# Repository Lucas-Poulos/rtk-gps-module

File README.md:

# rtk-gps-module

A cheap, solder-down **RTK GNSS module** that gets you centimetre-level
position. Dual-band L1 + L5, castellated edges, and a USB-C port so it also
works on its own with nothing but a cable.

**Status: schematic complete and verified. PCB layout is the next phase.**

```
    ┌──── u.FL ────┐
    │ active       │   50 Ω CPWG, 0.38 mm
    │ dual-band    ├──► ESD ─► bias tee ─► DC block ─► π ─► SAW ─┐
    │ antenna      │    0.25pF   68 nH      100 pF    0R   L1+L5 │
    └──────────────┘        ▲                                    ▼
                            │                            ┌───────────────┐
                    ANT_ON ─┴─ PMOS switch               │   LC29H (DA)  │
                                                         │  dual-band    │
    USB-C ─► ESD ─► BAT54C OR ─► AP2112K 3V3 ────────────┤  RTK rover    │
      │                ▲                                 │               │
      │             5V_IN (carrier)                      │  UART1  1PPS  │
      └─► CH340N ──────────────────────────── UART ──────┤               │
                                        1k/10k divider   └───────┬───────┘
                                                                 │
                              24 castellated pads, 1.27 mm ──────┘
```

## What it does

Feed it **RTCM3 corrections** over the UART — from an NTRIP client on a
phone, a Raspberry Pi or a PC — and it resolves carrier phase to **1–2 cm
horizontal**, versus the 2–3 m you get from ordinary GPS.

Corrections come from the host, so there is **no radio on the board**:
nothing to license, nothing to certify, and one less thing to pay for.

| | |
|---|---|
| Receiver | Quectel LC29H (DA), dual-band RTK rover |
| Bands | L1 / E1 / B1 / G1 **and** L5 / E5a / B2a |
| Constellations | GPS, GLONASS, Galileo, BeiDou, QZSS, SBAS |
| RTK accuracy | ~1–2 cm CEP, open sky |
| **RTK fix rate** | **1 Hz** — the DA does not go faster, see below |
| Position rate, no RTK | up to 10 Hz |
| Corrections in | RTCM3 over UART1 — MSM4 or MSM7, plus 1005/1006 |
| Timing out | 1PPS, rising-edge synchronised |
| Supply | 5 V from USB-C **or** 5 V from the carrier board |
| Logic | 3.3 V (plus a 1.8 V debug domain, see below) |
| Interface | USB-C (CH340N) and 24 castellated pads on 1.27 mm |
| **Parts cost** | **$27.10** per board at qty 1 |

The receiver is **88 % of the bill**. Everything else together is $1.56.
Nothing but the receiver is worth cost-optimising.

### RTK fixes at 1 Hz, and only 1 Hz

Quectel's *LC29H (BA,CA,DA,EA) DR&RTK Application Note* is unambiguous:

> LC29H (DA) only supports RTK (update rate: 1 Hz).
> LC29H (EA) only supports RTK (update rate: 1–10 Hz, 10 Hz by default).

The 10 Hz figure quoted for these modules is the ordinary position rate.
With RTK engaged, the DA produces **one fix per second**. If you need
faster, the only variant that does it is the **EA**, which costs roughly
25 % more than the DA and is a different board cost, not a firmware
setting.

This also means the **AA variant gives up nothing on rate**. Its raw
observations are capped at 1 Hz, which is exactly what the DA fixes at —
so "the AA is slower" is not a real objection to moving the RTK engine
onto the host.

### Where the corrections come from

The board has no radio, so RTCM3 arrives over UART1 from whatever the host
can reach. In the United States most states run a free CORS network.

In Massachusetts that is **MaCORS**, MassDOT's 22-station SpiderNet
network covering all 14 counties, free after registration at
`macors.massdot.state.ma.us`. It serves RTCM 3.1 and RTCM 3.2 MSM4.

That is directly compatible — no translation layer. The DA accepts:

| Message | |
|---|---|
| 1005 / 1006 | Stationary RTK Reference Station ARP |
| 1074 / 1077 | GPS MSM4 / MSM7 |
| 1084 / 1087 | GLONASS MSM4 / MSM7 |
| 1094 / 1097 | Galileo MSM4 / MSM7 |
| 1114 / 1117 | QZSS MSM4 / MSM7 |
| 1124 / 1127 | BeiDou MSM4 / MSM7 |

If the network offers a VRS mount point it synthesises a virtual base at
your position, so the usual "stay within ~1 km of the base" rule stops
applying — the effective baseline is short wherever you are inside the
network. Outside network coverage that rule returns, and the answer is
your own base: **`LC29HBS` is the base-station variant and shares this
footprint**, so a second board off the same fab run becomes one.

### Multipath will dominate your results before the board does

RTK resolves carrier phase, and carrier phase is ruined by reflections.
A signal bounced off a glass facade arrives with corrupted phase, which
costs you the fix — or worse, buys a confident but wrong one.

Test open-sky first and separate the two questions: *does the board work*
and *does it work where I need it*. Debugging the former in an urban
canyon wastes days.

## Everything else is discrete

There is no way to make an RTK receiver from discrete components — carrier
phase needs a correlator ASIC. So the receiver and its SAW filter are ICs
and *everything around them* is built from single transistors and passives
rather than bought as a block:

- **Antenna bias tee** — a 68 nH choke, a 100 pF block, and a PMOS/NPN pair
  switched by `ANT_ON`, with a 10 Ω resistor limiting a shorted antenna to
  ~330 mA.
- **5 V ORing** — one BAT54C, anodes to USB and to the carrier's 5 V,
  cathode to the LDO. USB and carrier power can both be present and neither
  back-feeds the other.
- **Backup domain** — a second BAT54C ORs 3V3 with an optional external
  cell on `VBCKP_EXT`, so the ephemeris cache survives and the module
  hot-starts in ~1 s instead of cold-starting in ~30 s.
- **RX level shift** — a 1 k / 10 k divider, because `RXD1` is specified
  VIHmax **3.08 V** and a 3.3 V host would exceed it.
- **1PPS indicator** — one MMBT3904, because 1PPS is guaranteed only 2.1 V
  high and would drive an LED dimly while loading the edge.

## The impedance work

Fully derived rather than asserted — see **[docs/impedance.md](docs/impedance.md)**.
Short version:

- The antenna line is a **conductor-backed CPWG**, not microstrip. Solving
  the conformal-mapping model for JLCPCB's 4-layer JLC04161H-3313 stackup
  gives **0.38 mm at 0.2 mm gap → 50.19 Ω**. Treating it as microstrip
  would say 0.41 mm and land it near 47 Ω.
- The SAW's ports are **50 Ω ∥ 5.1 nH**, not 50 Ω, so `L302`/`L303` are
  part of the impedance, not optional.
- The ESD diode is **0.25 pF**. An ordinary ESD part at 10–50 pF would
  shunt the antenna signal away.
- The number lives in `tools/calc_impedance.py`, and `make check` fails
  if the project's RF netclass drifts away from it.

## Pinout

24 castellated pads on 1.27 mm — drops onto 0.1 in perfboard.

**Left edge (J501)**

| Pad | Name | Notes |
|---:|---|---|
| 1 | GND | |
| 2 | 5V_IN | ORed with USB VBUS |
| 3 | 3V3 | LDO output |
| 4 | VBCKP_EXT | optional backup cell / supercap |
| 5 | GND | |
| 6 | TXD1 | receiver → host, NMEA / PQTM |
| 7 | RXD1 | host → receiver, RTCM3 in |
| 8 | 1PPS | rising edge |
| 9 | RESET_N | active low, pulled up on-board |
| 10 | WAKEUP | needs ≥ 3.0 V to wake |
| 11 | VDD_EXT | 2.8 V out, **100 mA max** |
| 12 | GND | |

**Right edge (J502)**

| Pad | Name | Notes |
|---:|---|---|
| 1 | GND | |
| 2 | ANT_ON | antenna switch control |
| 3 | I2C_SDA | via DNP link |
| 4 | I2C_SCL | via DNP link |
| 5 | TXD2 | **1.8 V domain**, via DNP link |
| 6 | RXD2 | **1.8 V domain**, via DNP link |
| 7 | D_SEL1 | **1.8 V domain**, via DNP link |
| 8 | D_SEL2 | **1.8 V domain**, via DNP link |
| 9 | GND | |
| 10–11 | — | spare |
| 12 | GND | |

> **Pads 5–8 on the right edge are not 3.3 V tolerant.** VIHmax is 2.1 V.
> Each reaches the edge only through an unfitted link, so a default board
> cannot present them to a 3.3 V host by accident.

`D_SEL1 = D_SEL2 = 0` selects UART1 and is the on-chip default via 75 kΩ
pulldowns, so the fitted board needs no strapping parts at all.

## Repository layout

```
design/        THE PROJECT. Open it in KiCad, edit it, save it.
  lib/         the two symbols and three footprints stock KiCad lacks
tools/         helpers that READ design/ -- none of them write to it
  check.py             ERC + netlist + sourcing + impedance
  gen_bom.py           BOM, read from the schematic
  calc_impedance.py    the 50 Ω derivation
  fetch_datasheets.py  pulls the vendor PDFs (not committed)
  bootstrap/           the generators that built v1 -- NOT authoritative
Makefile       run `make` to list every target
.githooks/     optional pre-commit hook, ERC errors only
manufacturing/ BOM.md, BOM-dnp.md, bom_jlcpcb.csv
docs/          editing.md, impedance.md, schematic.pdf
datasheets/    README + fetch script; the PDFs are not ours to redistribute
analysis/      ERC report and netlist (gitignored, regenerated on demand)
```

**`design/` is a normal KiCad project.** Edit it directly. Nothing
regenerates it, and nothing in `tools/` writes to it.

## Working on it

```bash
make open       # open in KiCad -- edit and save freely
make check      # ERC + netlist + sourcing + impedance, all read-only
make bom        # rebuild manufacturing/ after a parts change
make            # list every target
```

Read **[docs/editing.md](docs/editing.md)** before changing the RF path
or anything on the LC29H — there are four traps on this board that KiCad
will not warn you about (a 3.08 V limit on `RXD1`, a 1.8 V pin domain,
two supply pins that are outputs, and three pins that must float).

`make check` reads `design/` and never writes to it. It exports a fresh
netlist and a fresh ERC report and asserts against those:

- **ERC** — must be clean *and* the report must be newly written. A stale
  report from an earlier run reads exactly like a pass, and `kicad-cli`
  writes no report at all when the schematic fails to parse. Verified by
  injecting a deliberate fault and confirming ERC caught it on the right
  sub-sheet.
- **Netclass** — the exported per-net class is read back, because KiCad
  accepts a netclass pattern that matches nothing without complaining and
  a 50 Ω line silently falls back to the default track width. *(This
  caught a real bug: `/regex/` patterns are accepted by the file format
  and match nothing — KiCad uses wildcards, and local nets carry their
  sheet path.)*
- **Critical nets** — the RF chain, the bias tee and the RXD1 divider are
  asserted pin by pin, so none of them gets rerouted by accident. Rewire
  one on purpose and it tells you exactly what changed.
- **LC29H pin rules** — grounds grounded, the three RESERVED pins still
  floating, `VDD_EXT` never tied to 3V3.
- **Sourcing** — every fitted part must carry a resolved `Cxxxxx`.
- **Impedance** — the RF netclass width must still match what
  `tools/calc_impedance.py` derives, and still land within 5 % of 50 Ω.

## Building one

The BOM is in [manufacturing/BOM.md](manufacturing/BOM.md), with
`bom_jlcpcb.csv` ready for JLCPCB assembly and
[BOM-dnp.md](manufacturing/BOM-dnp.md) listing the unfitted options.

Prices and stock were read from LCSC on 2026-09-28 and frozen for
traceability — **re-check before ordering.** LC29H stock in particular was
thin (22 pcs). `LC29HBS` (`C21385845`) is the RTK *base station* variant and
`LC29HAA` (`C22403415`) has no RTK engine; both share the footprint, so
check you are buying the one you mean.

You also need an **active dual-band L1+L5 antenna** with NF < 1.5 dB, gain
< 17 dB, and its SAW ahead of its LNA.

## Caveats

- **Not built yet.** The schematic is verified; no board has been
  fabricated, so nothing here is confirmed against hardware.
- **The LC29H (DA) pinout is contested by its own datasheet.** Figure 4
  and Table 6 disagree about pins 15–19. The V1.3 revision history settles
  it in Table 6's favour (the changes applied only to the EA variant), and
  the design follows Table 6 — but those four pins reach the edge only
  through unfitted links, so the board is correct either way.
- Prices are a snapshot, not a quote.

## Licence

Hardware under [CERN-OHL-P v2](LICENSE); the scripts under the same terms.
Permissive — do what you like, no reciprocity required.

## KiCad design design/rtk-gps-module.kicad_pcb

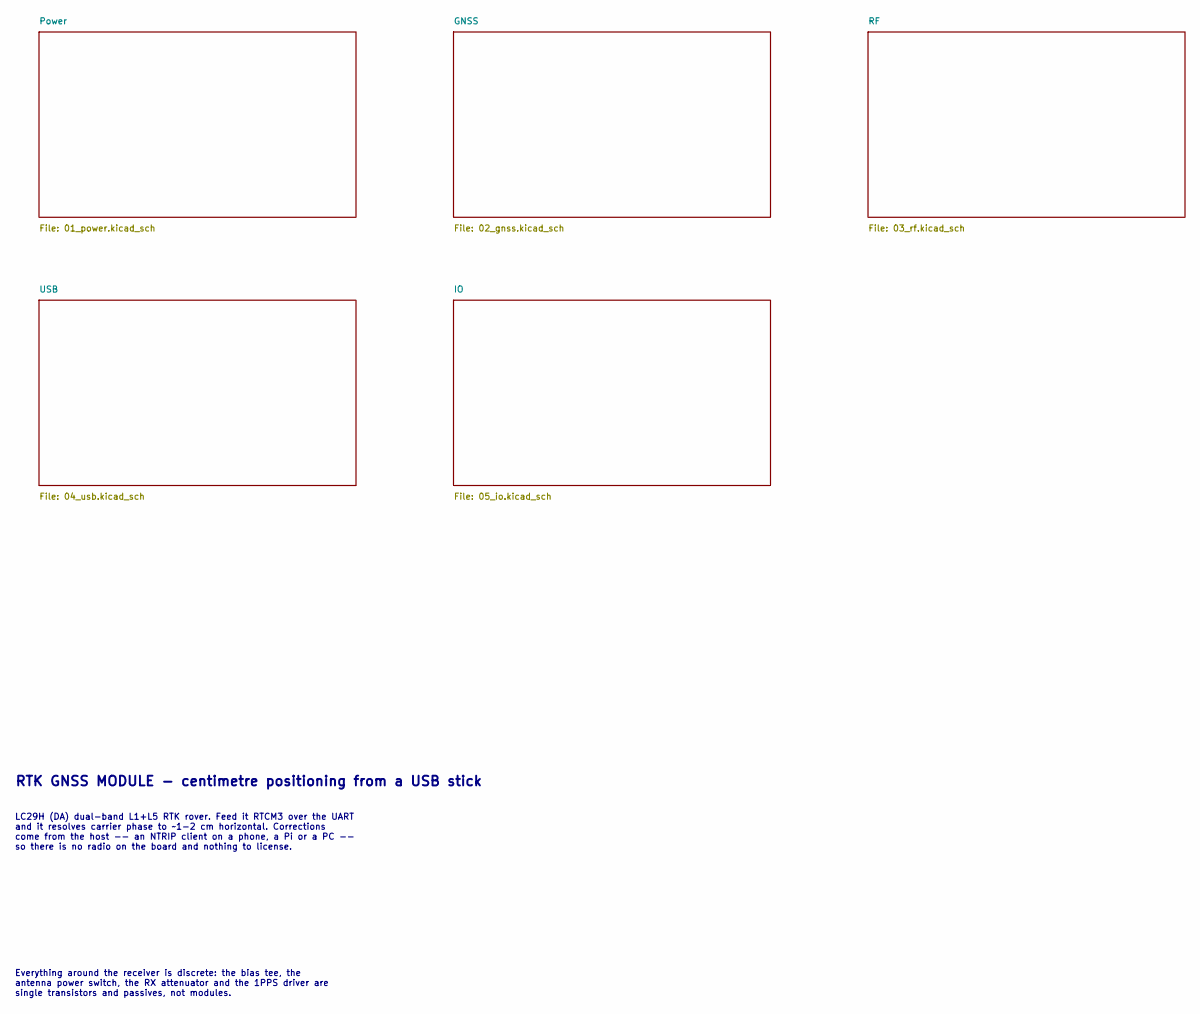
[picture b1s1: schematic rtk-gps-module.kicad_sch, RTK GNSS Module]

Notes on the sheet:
RTK GNSS MODULE - centimetre positioning from a USB stick
Everything around the receiver is discrete: the bias tee, the antenna power switch, the RX attenuator and the 1PPS driver are single transistors and passives, not modules.
LC29H (DA) dual-band L1+L5 RTK rover. Feed it RTCM3 over the UART and it resolves carrier phase to ~1-2 cm horizontal. Corrections come from the host -- an NTRIP client on a phone, a Pi or a PC -- so there is no radio on the board and nothing to license.

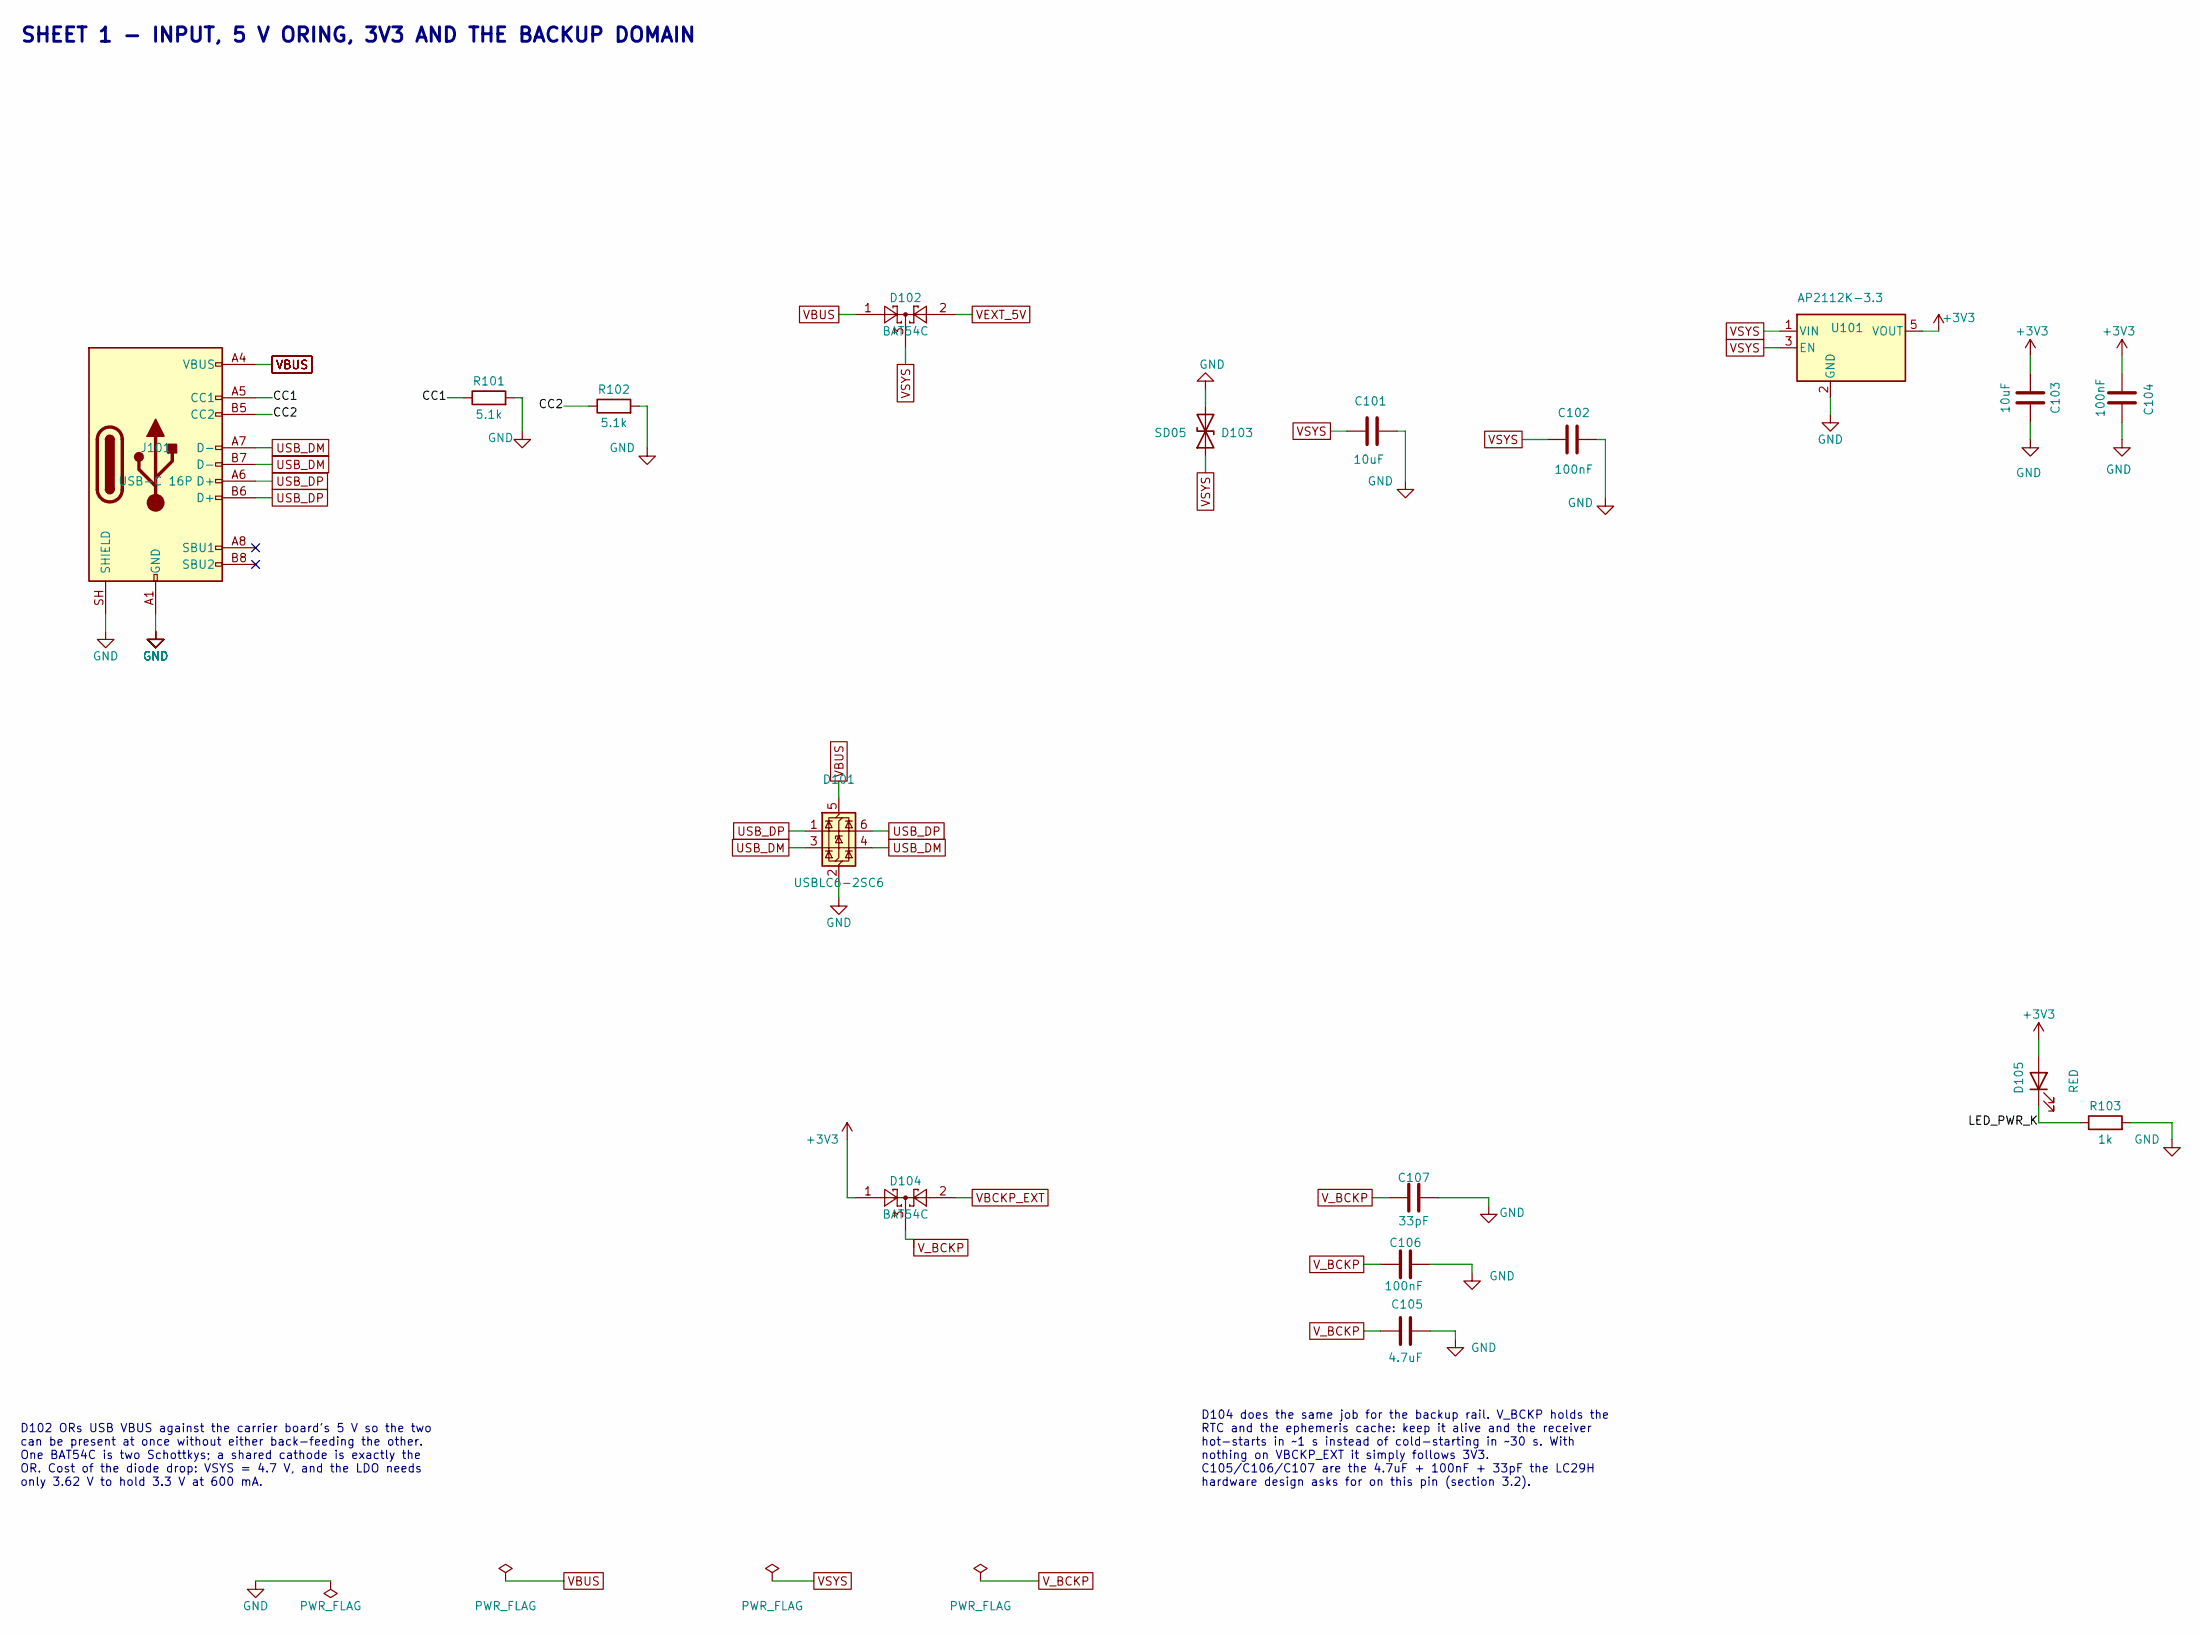
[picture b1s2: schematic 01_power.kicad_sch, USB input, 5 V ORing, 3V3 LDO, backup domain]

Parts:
C101, C103: 10uF; C_0805_2012Metric; MPN CL21A106KAYNNNE; LCSC C15850
C102, C104, C106: 100nF; C_0402_1005Metric; MPN CL05B104KO5NNNC; LCSC C1525
C105: 4.7uF; C_0603_1608Metric; MPN CL10A475KO8NNNC; LCSC C19666
C107: 33pF; C_0402_1005Metric; MPN 0402CG330J500NT; LCSC C1562
D101: USBLC6-2SC6; SOT-23-6; MPN USBLC6-2SC6; LCSC C2827654
D102, D104: BAT54C; SOT-23; MPN BAT54C; LCSC C916424
D103: SD05; D_SOD-323; MPN SD05; LCSC C502527
D105: RED; LED_0603_1608Metric; MPN KT-0603R; LCSC C2286
J101: USB-C 16P; USB_C_Receptacle_HRO_TYPE-C-31-M-12; MPN TYPE-C 16PIN 2MD(073); LCSC C2765186
R101, R102: 5.1k; R_0402_1005Metric; Tolerance 1%; MPN 0402WGF5101TCE; LCSC C25905
R103: 1k; R_0402_1005Metric; Tolerance 1%; MPN 0402WGF1001TCE; LCSC C11702
U101: AP2112K-3.3; SOT-23-5; MPN AP2112K-3.3TRG1; LCSC C23380830

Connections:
+3V3: C103.1, C104.1, D104.1, D105.2 (A), U101.5 (VOUT); also elsewhere on the board
/Power/CC1: J101.A5 (CC1), R101.1
/Power/CC2: J101.B5 (CC2), R102.1
/Power/LED_PWR_K: D105.1 (K), R103.1
GND: C101.2, C102.2, C103.2, C104.2, C105.2, C106.2, C107.2, D101.2 (GND), D103.2 (A2), J101.A1 (GND), J101.A12 (GND), J101.B1 (GND), J101.B12 (GND), J101.SH (SHIELD), R101.2, R102.2, R103.2, U101.2 (GND); also elsewhere on the board
USB_DM: D101.3 (I/O2), D101.4 (I/O2), J101.A7 (D-), J101.B7 (D-); also elsewhere on the board
USB_DP: D101.1 (I/O1), D101.6 (I/O1), J101.A6 (D+), J101.B6 (D+); also elsewhere on the board
VBCKP_EXT: D104.2; also elsewhere on the board
VBUS: D101.5 (VBUS), D102.1, J101.A4 (VBUS), J101.A9 (VBUS), J101.B4 (VBUS), J101.B9 (VBUS)
VEXT_5V: D102.2; also elsewhere on the board
VSYS: C101.1, C102.1, D102.3, D103.1 (A1), U101.1 (VIN), U101.3 (EN)
V_BCKP: C105.1, C106.1, C107.1, D104.3; also elsewhere on the board

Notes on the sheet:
D102 ORs USB VBUS against the carrier board's 5 V so the two can be present at once without either back-feeding the other. One BAT54C is two Schottkys; a shared cathode is exactly the OR. Cost of the diode drop: VSYS = 4.7 V, and the LDO needs only 3.62 V to hold 3.3 V at 600 mA.
SHEET 1 - INPUT, 5 V ORING, 3V3 AND THE BACKUP DOMAIN
D104 does the same job for the backup rail. V_BCKP holds the RTC and the ephemeris cache: keep it alive and the receiver hot-starts in ~1 s instead of cold-starting in ~30 s. With nothing on VBCKP_EXT it simply follows 3V3. C105/C106/C107 are the 4.7uF + 100nF + 33pF the LC29H hardware design asks 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

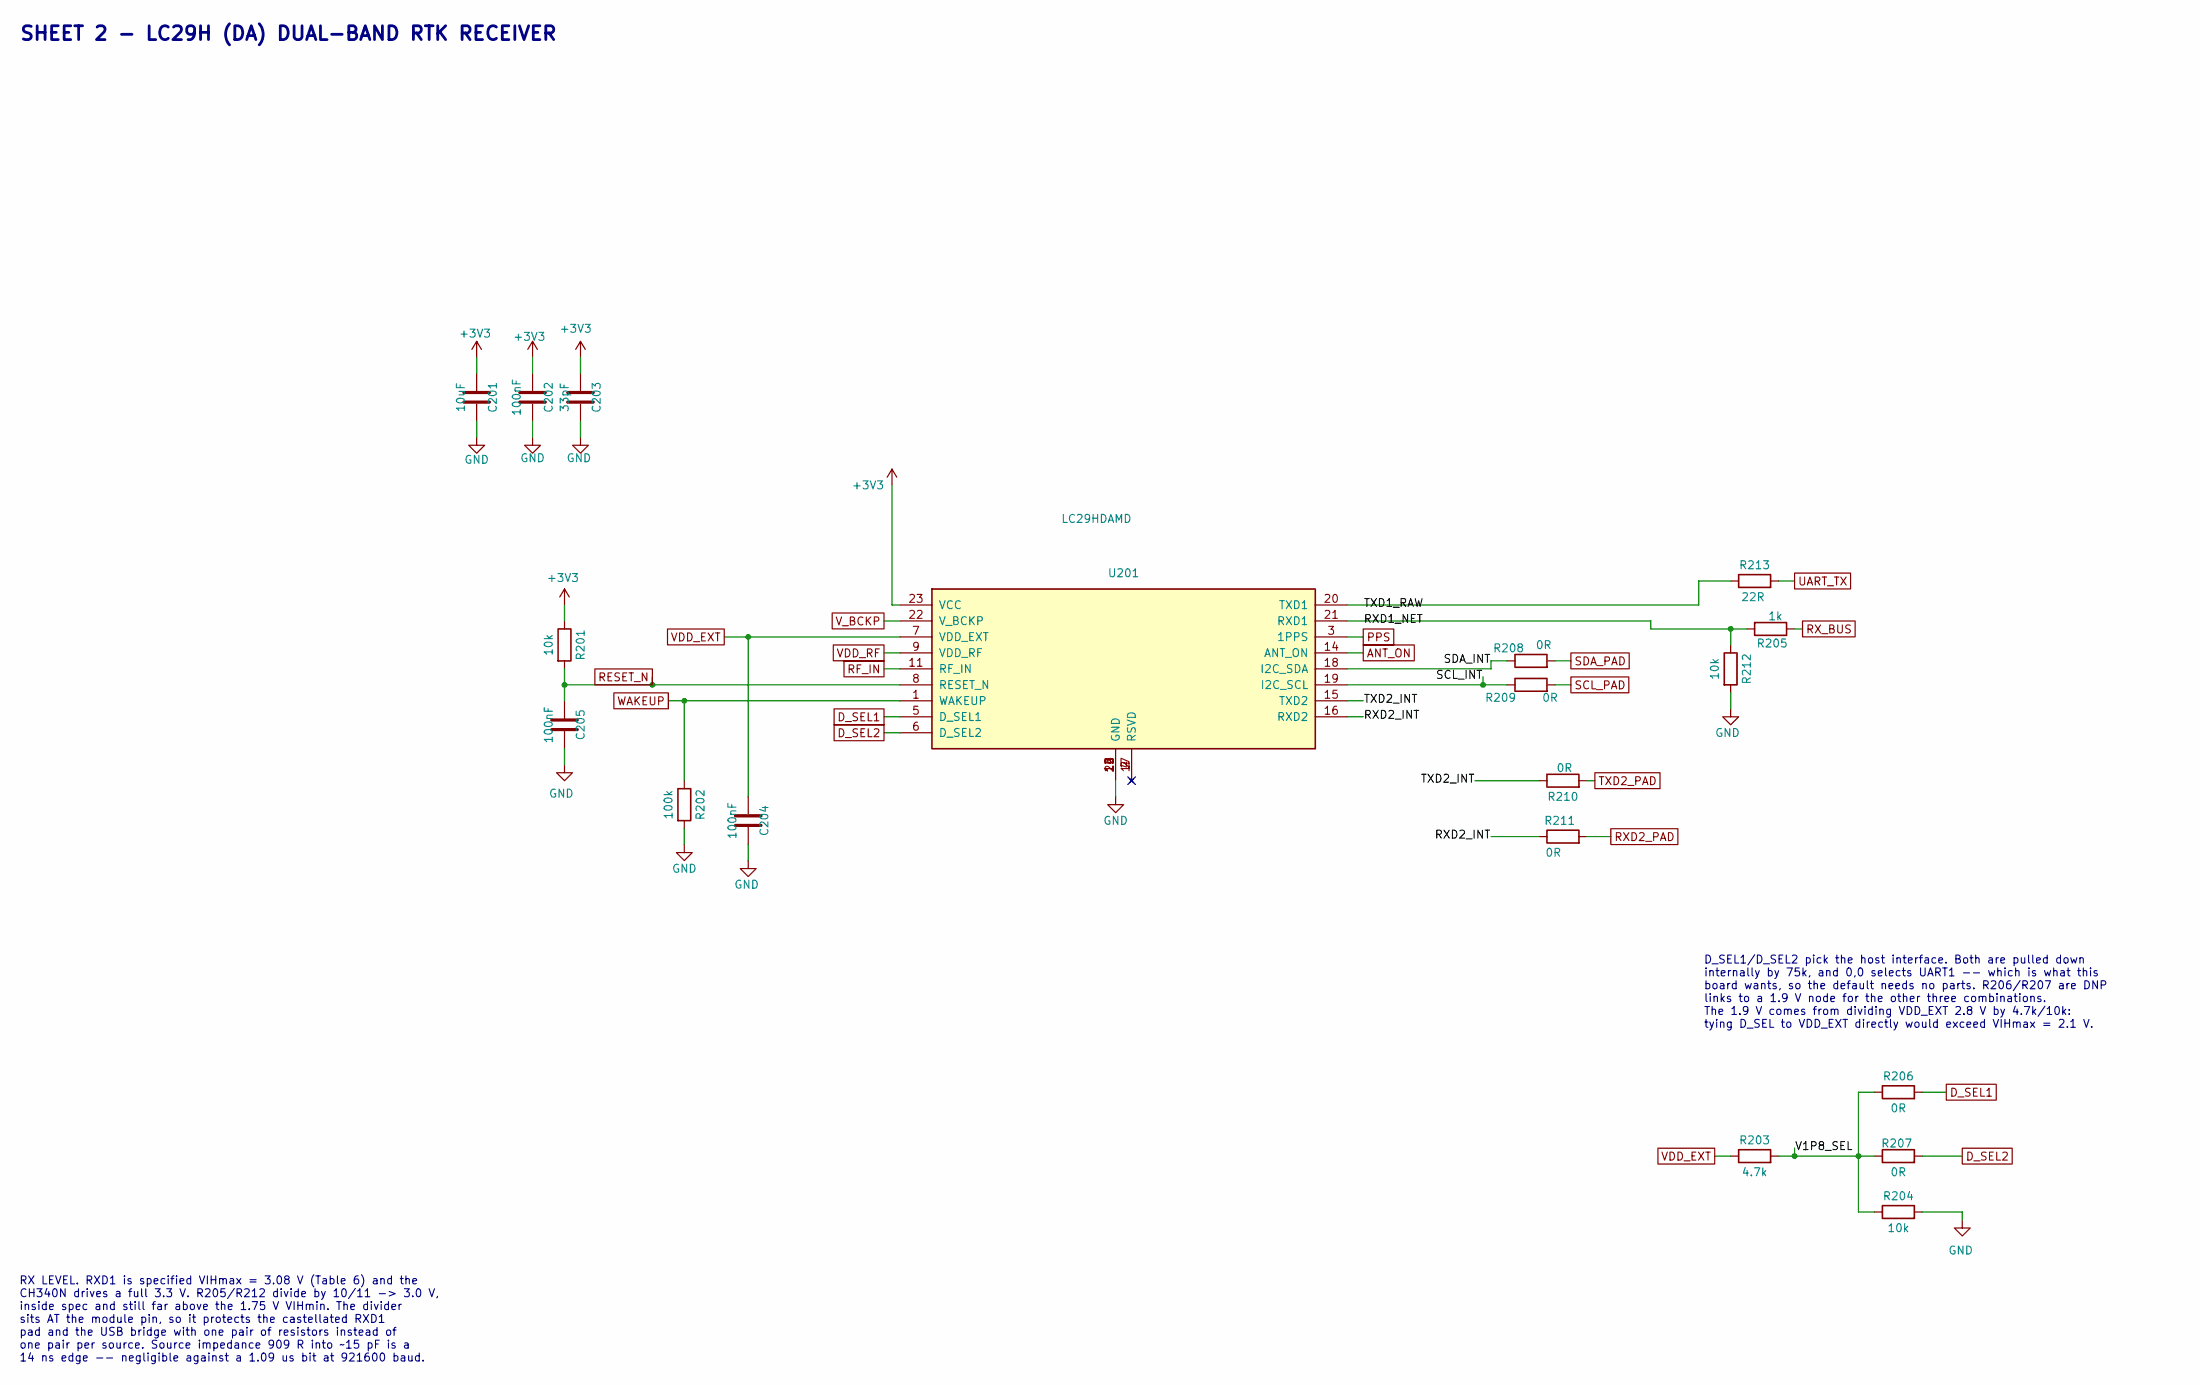
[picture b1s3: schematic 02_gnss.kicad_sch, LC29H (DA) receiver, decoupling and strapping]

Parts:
C201: 10uF; C_0805_2012Metric; MPN CL21A106KAYNNNE; LCSC C15850
C202, C204, C205: 100nF; C_0402_1005Metric; MPN CL05B104KO5NNNC; LCSC C1525
C203: 33pF; C_0402_1005Metric; MPN 0402CG330J500NT; LCSC C1562
R201, R204, R212: 10k; R_0402_1005Metric; Tolerance 1%; MPN 0402WGF1002TCE; LCSC C25744
R202: 100k; R_0402_1005Metric; Tolerance 1%; MPN 0402WGF1003TCE; LCSC C25741
R203: 4.7k; R_0402_1005Metric; Tolerance 1%; MPN 0402WGF4701TCE; LCSC C25900
R205: 1k; R_0402_1005Metric; Tolerance 1%; MPN 0402WGF1001TCE; LCSC C11702
R206, R207, R208, R209, R210, R211: 0R; R_0402_1005Metric; Tolerance 1%; MPN 0402WGF0000TCE; LCSC C17168
R213: 22R; R_0402_1005Metric; Tolerance 1%; MPN 0402WGF220JTCE; LCSC C25092
U201: LC29HDAMD; Quectel_LC29H_LCC-24_12.2x16.0mm; MPN LC29HDAMD; LCSC C20748061

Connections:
+3V3: C201.1, C202.1, C203.1, R201.1, U201.23 (VCC); also elsewhere on the board
/GNSS/RXD1_NET: R205.2, R212.1, U201.21 (RXD1)
/GNSS/RXD2_INT: R211.1, U201.16 (RXD2)
/GNSS/SCL_INT: R209.1, U201.19 (I2C_SCL)
/GNSS/SDA_INT: R208.1, U201.18 (I2C_SDA)
/GNSS/TXD1_RAW: R213.1, U201.20 (TXD1)
/GNSS/TXD2_INT: R210.1, U201.15 (TXD2)
/GNSS/V1P8_SEL: R203.2, R204.1, R206.1, R207.1
ANT_ON: U201.14 (ANT_ON); also elsewhere on the board
D_SEL1: R206.2, U201.5 (D_SEL1); also elsewhere on the board
D_SEL2: R207.2, U201.6 (D_SEL2); also elsewhere on the board
GND: C201.2, C202.2, C203.2, C204.2, C205.2, R202.2, R204.2, R212.2, U201.10 (GND), U201.12 (GND), U201.13 (GND), U201.24 (GND); also elsewhere on the board
PPS: U201.3 (1PPS); also elsewhere on the board
RESET_N: C205.1, R201.2, U201.8 (RESET_N); also elsewhere on the board
RF_IN: U201.11 (RF_IN); also elsewhere on the board
RXD2_PAD: R211.2; also elsewhere on the board
RX_BUS: R205.1; also elsewhere on the board
SCL_PAD: R209.2; also elsewhere on the board
SDA_PAD: R208.2; also elsewhere on the board
TXD2_PAD: R210.2; also elsewhere on the board
UART_TX: R213.2; also elsewhere on the board
VDD_EXT: C204.1, R203.1, U201.7 (VDD_EXT); also elsewhere on the board
VDD_RF: U201.9 (VDD_RF); also elsewhere on the board
V_BCKP: U201.22 (V_BCKP); also elsewhere on the board
WAKEUP: R202.1, U201.1 (WAKEUP); also elsewhere on the board

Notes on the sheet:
D_SEL1/D_SEL2 pick the host interface. Both are pulled down internally by 75k, and 0,0 selects UART1 -- which is what this board wants, so the default needs no parts. R206/R207 are DNP links to a 1.9 V node for the other three combinations. The 1.9 V comes from dividing VDD_EXT 2.8 V by 4.7k/10k: t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
RX LEVEL. RXD1 is specified VIHmax = 3.08 V (Table 6) and the CH340N drives a full 3.3 V. R205/R212 divide by 10/11 -> 3.0 V, inside spec and still far above the 1.75 V VIHmin. The divider sits AT the module pin, so it protects the castellated RXD1 pad and the USB bridge with one pair of resistors 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
SHEET 2 - LC29H (DA) DUAL-BAND RTK RECEIVER

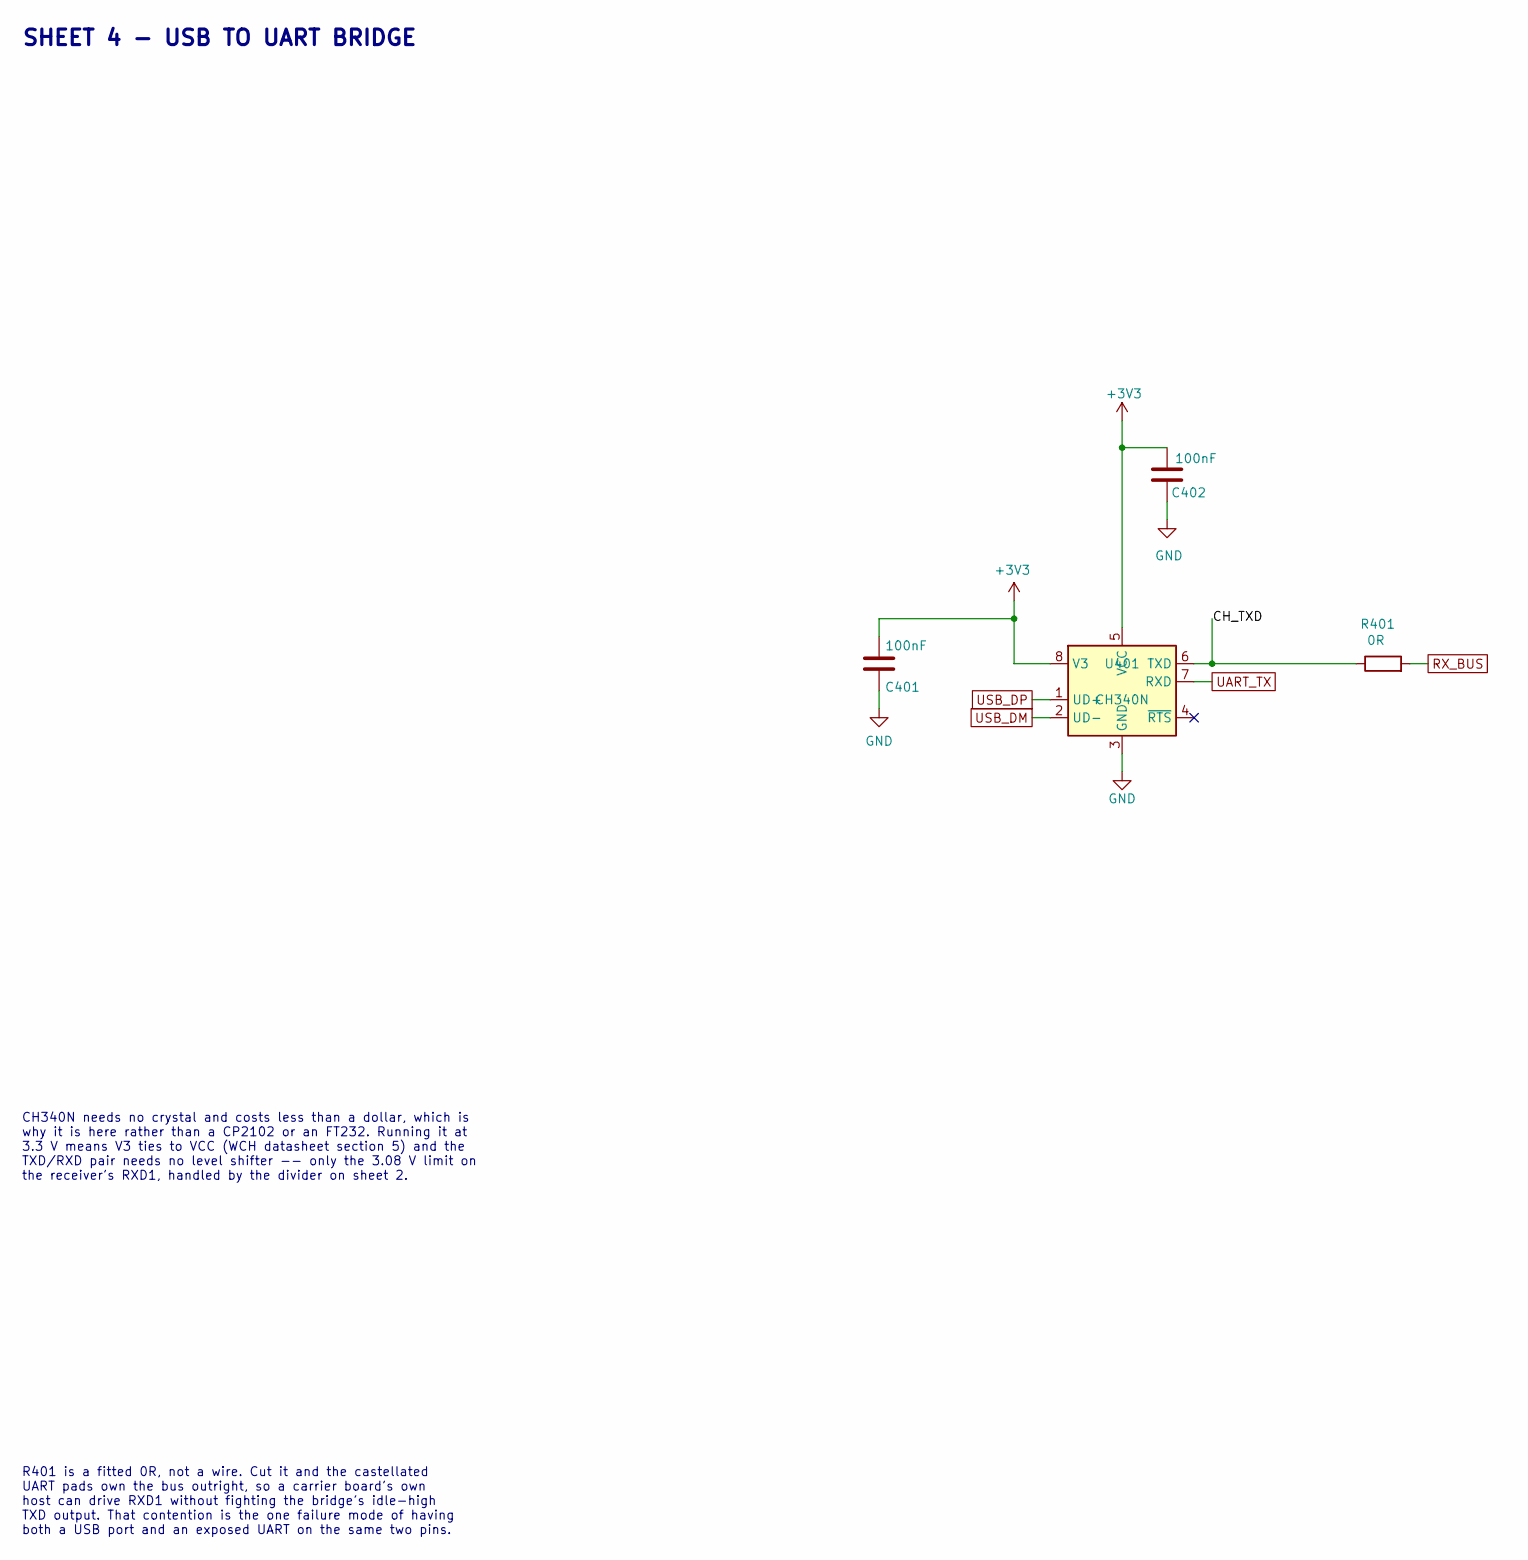
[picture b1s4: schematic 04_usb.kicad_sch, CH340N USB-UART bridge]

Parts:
C401, C402: 100nF; C_0402_1005Metric; MPN CL05B104KO5NNNC; LCSC C1525
R401: 0R; R_0402_1005Metric; Tolerance 1%; MPN 0402WGF0000TCE; LCSC C17168
U401: CH340N; SOIC-8_3.9x4.9mm_P1.27mm; MPN CH340N; LCSC C2977777

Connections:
+3V3: C401.1, C402.1, U401.5 (VCC), U401.8 (V3); also elsewhere on the board
/USB/CH_TXD: R401.1, U401.6 (TXD)
GND: C401.2, C402.2, U401.3 (GND); also elsewhere on the board
RX_BUS: R401.2; also elsewhere on the board
UART_TX: U401.7 (RXD); also elsewhere on the board
USB_DM: U401.2 (UD-); also elsewhere on the board
USB_DP: U401.1 (UD+); also elsewhere on the board

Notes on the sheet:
R401 is a fitted 0R, not a wire. Cut it and the castellated UART pads own the bus outright, so a carrier board's own host can drive RXD1 without fighting the bridge's idle-high TXD output. That contention is the one failure mode of having both a USB port and an exposed UART on the same two pins.
CH340N needs no crystal and costs less than a dollar, which is why it is here rather than a CP2102 or an FT232. Running it at 3.3 V means V3 ties to VCC (WCH datasheet section 5) and the TXD/RXD pair needs no level shifter -- only the 3.08 V limit on the receiver's RXD1, handled by the divider on s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
SHEET 4 - USB TO UART BRIDGE

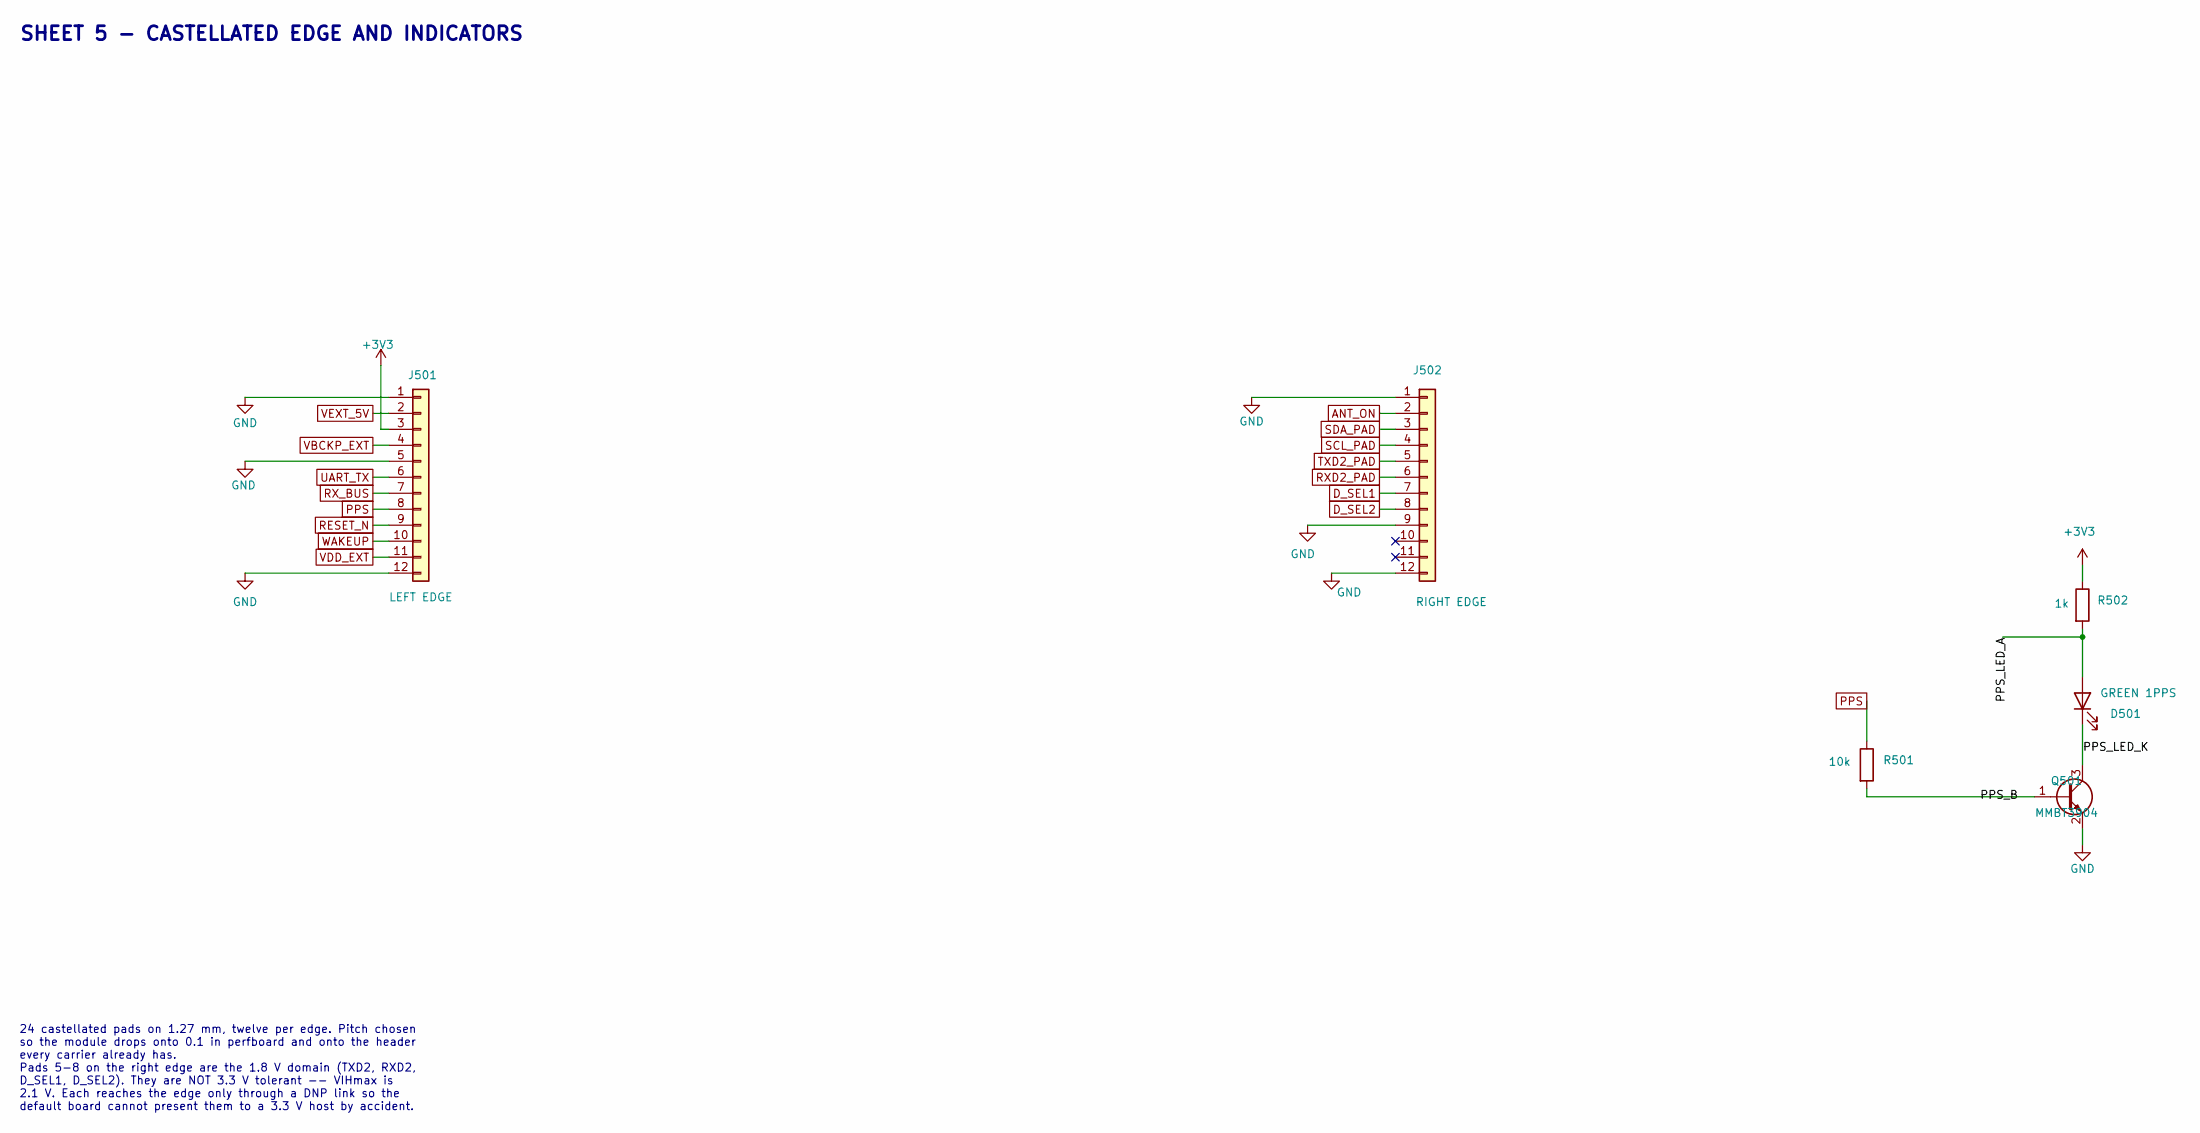
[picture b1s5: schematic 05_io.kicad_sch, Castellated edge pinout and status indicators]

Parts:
D501: GREEN 1PPS; LED_0603_1608Metric; MPN KT-0603G; LCSC C12624
J501: LEFT EDGE; Castellated_1x12_P1.27mm
J502: RIGHT EDGE; Castellated_1x12_P1.27mm
Q501: MMBT3904; SOT-23; MPN MMBT3904; LCSC C20526
R501: 10k; R_0402_1005Metric; Tolerance 1%; MPN 0402WGF1002TCE; LCSC C25744
R502: 1k; R_0402_1005Metric; Tolerance 1%; MPN 0402WGF1001TCE; LCSC C11702

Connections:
+3V3: J501.3, R502.1; also elsewhere on the board
/IO/PPS_B: Q501.1 (B), R501.2
/IO/PPS_LED_A: D501.2 (A), R502.2
/IO/PPS_LED_K: D501.1 (K), Q501.3 (C)
ANT_ON: J502.2; also elsewhere on the board
D_SEL1: J502.7; also elsewhere on the board
D_SEL2: J502.8; also elsewhere on the board
GND: J501.1, J501.5, J501.12, J502.1, J502.9, J502.12, Q501.2 (E); also elsewhere on the board
PPS: J501.8, R501.1; also elsewhere on the board
RESET_N: J501.9; also elsewhere on the board
RXD2_PAD: J502.6; also elsewhere on the board
RX_BUS: J501.7; also elsewhere on the board
SCL_PAD: J502.4; also elsewhere on the board
SDA_PAD: J502.3; also elsewhere on the board
TXD2_PAD: J502.5; also elsewhere on the board
UART_TX: J501.6; also elsewhere on the board
VBCKP_EXT: J501.4; also elsewhere on the board
VDD_EXT: J501.11; also elsewhere on the board
VEXT_5V: J501.2; also elsewhere on the board
WAKEUP: J501.10; also elsewhere on the board

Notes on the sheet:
24 castellated pads on 1.27 mm, twelve per edge. Pitch chosen so the module drops onto 0.1 in perfboard and onto the header every carrier already has. Pads 5-8 on the right edge are the 1.8 V domain (TXD2, RXD2, D_SEL1, D_SEL2). They are NOT 3.3 V tolerant -- VIHmax is 2.1 V. Each reaches the edge 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
SHEET 5 - CASTELLATED EDGE AND INDICATORS
